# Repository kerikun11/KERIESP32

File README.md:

# KERIESP32
An ESP32 Development Board made by KERI

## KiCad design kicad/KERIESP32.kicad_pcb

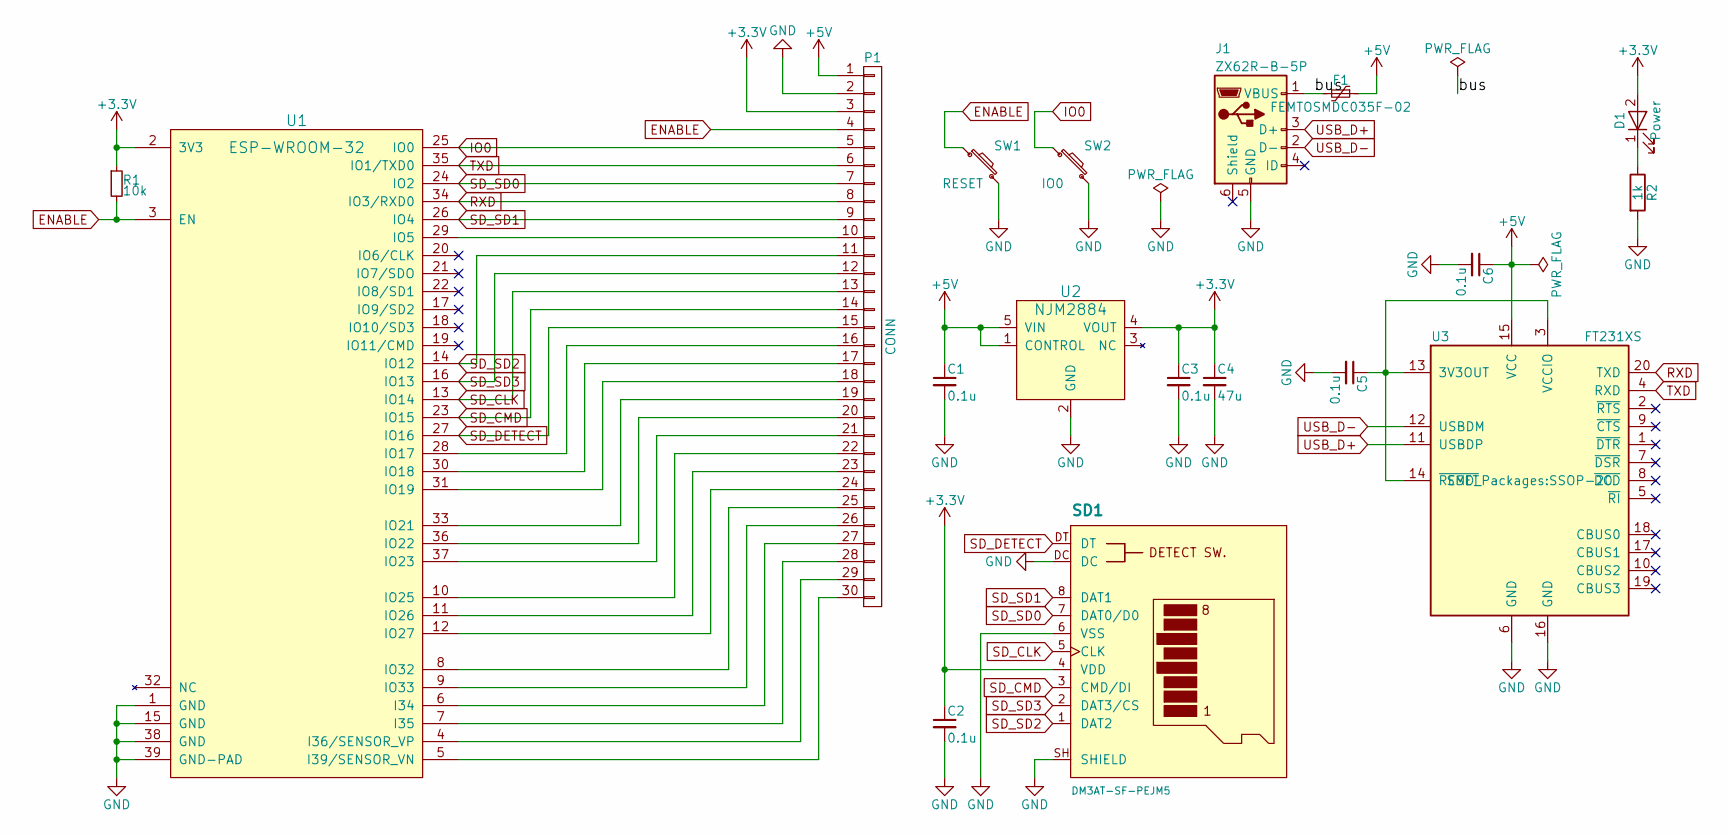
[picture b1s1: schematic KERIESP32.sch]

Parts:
C1, C2, C3, C5, C6: 0.1u; C_0603
C4: 47u; C_1206
D1: Power; LED_0603
F1: FEMTOSMDC035F-02; C_0603
J1: ZX62R-B-5P
P1: CONN; Pin_Header_Straight_1x30_Pitch2.54mm
R1: 10k; R_0603
R2: 1k; R_0603
SD1: DM3AT-SF-PEJM5; HIROSE-MICROSD-DM3AT-SF
SW1: RESET; SW_PUSH
SW2: IO0; SW_PUSH
U1: ESP-WROOM-32
U2: NJM2884; SOT89-5_Housing
U3: FT231XS; SSOP-20

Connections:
+3V3: C2.1, C3.1, C4.1, D1.2 (A), P1.3, R1.1, SD1.4 (VDD), U1.2 (3V3), U2.4 (VOUT)
+5V: C1.1, C6.1, F1.1, P1.1, U2.1 (CONTROL), U2.5 (VIN), U3.15 (VCC)
/bus: F1.2, J1.1 (VBUS)
ENABLE: P1.4, R1.2, SW1.1, U1.3 (EN)
GND: C1.2, C2.2, C3.2, C4.2, C5.2, C6.2, J1.5 (GND), P1.2, R2.2, SD1.6 (VSS), SD1.DC, SD1.SH (SHIELD), SW1.2, SW2.2, U1.1 (GND), U1.15 (GND), U1.38 (GND), U1.39 (GND-PAD), U2.2 (GND), U3.6 (GND), U3.16 (GND)
IO0: P1.5, SW2.1, U1.25 (IO0)
unnamed: C5.1, U3.3 (VCCIO), U3.13 (3V3OUT), U3.14 (~RESET)
unnamed: D1.1 (K), R2.1
unnamed: P1.10, U1.29 (IO5)
unnamed: P1.16, U1.28 (IO17)
unnamed: P1.17, U1.30 (IO18)
unnamed: P1.18, U1.31 (IO19)
unnamed: P1.19, U1.33 (IO21)
unnamed: P1.20, U1.36 (IO22)
unnamed: P1.21, U1.37 (IO23)
unnamed: P1.22, U1.10 (IO25)
unnamed: P1.23, U1.11 (IO26)
unnamed: P1.24, U1.12 (IO27)
unnamed: P1.25, U1.8 (IO32)
unnamed: P1.26, U1.9 (IO33)
unnamed: P1.27, U1.6 (I34)
unnamed: P1.28, U1.7 (I35)
unnamed: P1.29, U1.4 (I36/SENSOR_VP)
unnamed: P1.30, U1.5 (I39/SENSOR_VN)
RXD: P1.8, U1.34 (IO3/RXD0), U3.20 (TXD)
SD_CLK: P1.13, SD1.5 (CLK), U1.13 (IO14)
SD_CMD: P1.14, SD1.3 (CMD/DI), U1.23 (IO15)
SD_DETECT: P1.15, SD1.DT, U1.27 (IO16)
SD_SD0: P1.7, SD1.7 (DAT0/D0), U1.24 (IO2)
SD_SD1: P1.9, SD1.8 (DAT1), U1.26 (IO4)
SD_SD2: P1.11, SD1.1 (DAT2), U1.14 (IO12)
SD_SD3: P1.12, SD1.2 (DAT3/CS), U1.16 (IO13)
TXD: P1.6, U1.35 (IO1/TXD0), U3.4 (RXD)
USB_D+: J1.3 (D+), U3.11 (USBDP)
USB_D-: J1.2 (D-), U3.12 (USBDM)

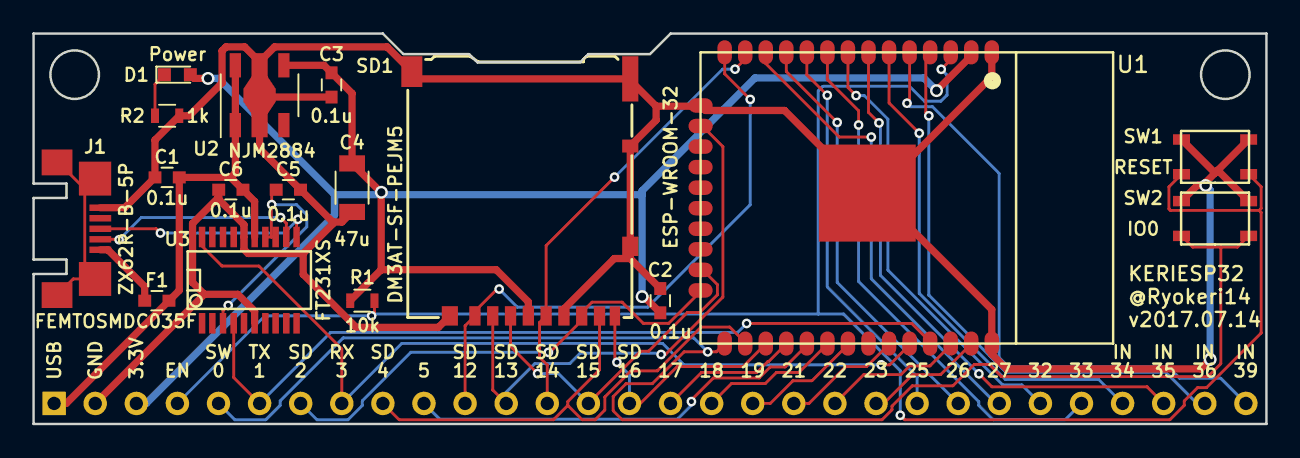
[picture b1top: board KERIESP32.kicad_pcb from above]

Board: 2 copper layers, 76.2 x 24.1 mm, 18 parts (1 on the bottom side), 35 nets.

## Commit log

2017-02-23 KiCadファイルを追加
2017-03-02 部品表，回路図PDFを生成
2017-04-09 台形型変換基板を設計
2017-04-12 台形基板にSDカードを設置
    裏面にMicroSDスロットを取り付け．
    形は変わらず
2017-07-07 ブレッドボード用の基板を設計SIP
2017-07-14 小型化，自動配線成功
2017-07-14 マイクロSDのクリアランスの修正
2017-07-14 4枚面付け基板作成
2017-07-23 表示の修正
2017-08-01 回路図を整理
    PDFを出力
